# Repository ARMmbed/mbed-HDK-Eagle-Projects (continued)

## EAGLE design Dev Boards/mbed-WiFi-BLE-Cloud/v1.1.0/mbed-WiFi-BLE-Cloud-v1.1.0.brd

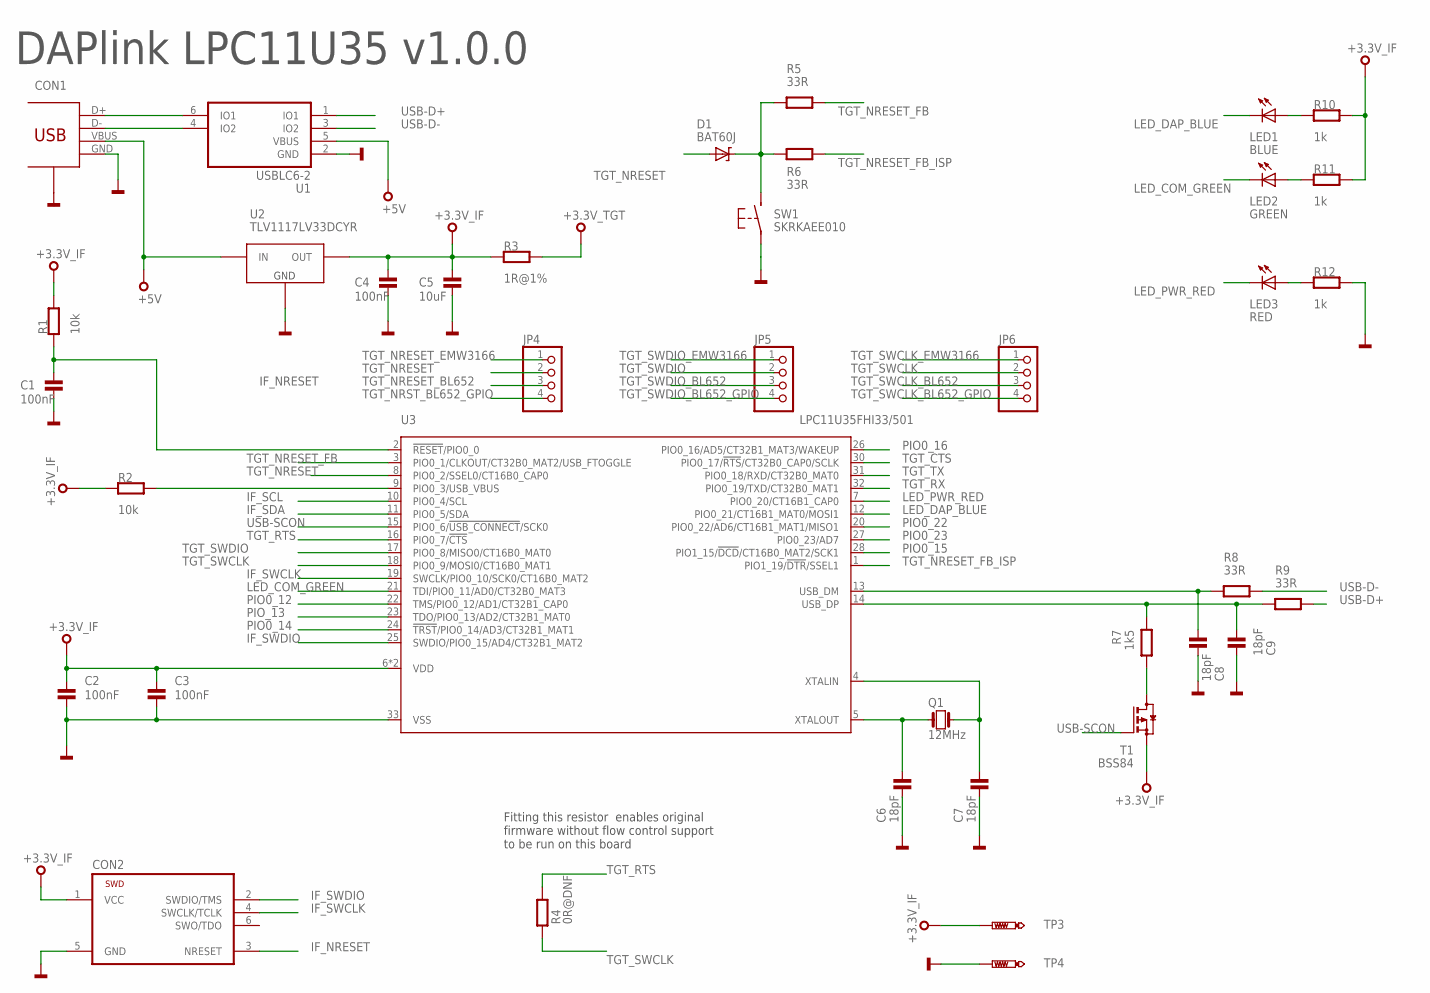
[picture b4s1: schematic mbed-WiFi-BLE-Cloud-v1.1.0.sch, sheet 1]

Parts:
C1, C2, C3, C4: 100nF; 0603
C5: 10uF; 0603
C6, C7, C8, C9: 18pF; 0603
CON1: 47346-0001; USB-MICRO-B-H
CON2: TC2030-CTX-NL
D1: BAT60J; SOD323
JP4, JP5, JP6: PINHD-1X4; 1X04
LED1: BLUE; CHIPLED_0603
LED2: GREEN; CHIPLED_0603
LED3: RED; CHIPLED_0603
Q1: 12MHz; 3.2X2.5
R1, R2: 10k; 0603
R3: 1R@1%; 0603
R4: 0R@DNF; 0603
R5, R6, R8, R9: 33R; 0603
R7: 1k5; 0603
R10, R11, R12: 1k; 0603
SW1: SKRKAEE010
T1: BSS84; SOT23-3
TP3, TP4: PTR1PAD1-13; P1-13
U1: USBLC6-2SC6; SOT23-6L
U2: TLV1117LV33DCYR; SOT223
U3: LPC11U35FHI33/501; SOT617-3

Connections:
+3.3V_IF: C2.1, C3.1, C4.1, C5.1, CON2.1 (VCC), R1.2, R2.1, R3.1, R10.2, R11.2, T1.2 (S), TP3.TP, U2.2 (OUT), U2.4 (OUT), U3.6 (VDD), U3.29 (VDD); also elsewhere on the board
+3.3V_TGT: R3.2; also elsewhere on the board
+5V: CON1.VBUS, U1.5 (VBUS), U2.3 (IN); also elsewhere on the board
GND: C1.2, C2.2, C3.2, C4.2, C5.2, C6.2, C7.2, C8.2, C9.2, CON1.GND, CON1.GND1 (SHEILD), CON1.GND2 (SHEILD), CON1.GND3 (SHEILD), CON1.GND4 (SHEILD), CON2.5 (GND), R12.2, SW1.P$1, TP4.TP, U1.2 (GND), U2.1 (GND), U3.33 (VSS); also elsewhere on the board
IF_NRESET: C1.1, CON2.3 (NRESET), R1.1, U3.2 (!RESET!/PIO0_0)
IF_SCL: U3.10 (PIO0_4/SCL); also elsewhere on the board
IF_SDA: U3.11 (PIO0_5/SDA); also elsewhere on the board
IF_SWCLK: CON2.4 (SWCLK/TCLK), U3.19 (SWCLK/PIO0_10/SCK0/CT16B0_MAT2)
IF_SWDIO: CON2.2 (SWDIO/TMS), U3.25 (SWDIO/PIO0_15/AD4/CT32B1_MAT2)
LED_COM_GREEN: LED2.C, U3.21 (TDI/PIO0_11/AD0/CT32B0_MAT3)
LED_DAP_BLUE: LED1.C, U3.12 (PIO0_21/CT16B1_MAT0/MOSI1)
LED_PWR_RED: LED3.C, U3.7 (PIO0_20/CT16B1_CAP0)
unnamed: C7.1, Q1.P$3 (2), U3.4 (XTALIN)
unnamed: R7.1, T1.3 (D)
unnamed: CON1.D+, U1.6 (IO1)
unnamed: CON1.D-, U1.4 (IO2)
unnamed: C6.1, Q1.P$1 (1), U3.5 (XTALOUT)
unnamed: R2.2, U3.9 (PIO0_3/USB_VBUS)
unnamed: LED2.A, R11.1
unnamed: LED1.A, R10.1
unnamed: LED3.A, R12.1
PIO0_12: U3.22 (TMS/PIO0_12/AD1/CT32B1_CAP0)
PIO0_14: U3.24 (!TRST!/PIO0_14/AD3/CT32B1_MAT1)
PIO0_15: U3.28 (PIO1_15/!DCD!/CT16B0_MAT2/SCK1)
PIO0_16: U3.26 (PIO0_16/AD5/CT32B1_MAT3/WAKEUP)
PIO0_22: U3.20 (PIO0_22/AD6/CT16B1_MAT1/MISO1)
PIO0_23: U3.27 (PIO0_23/AD7)
PIO_13: U3.23 (TDO/PIO0_13/AD2/CT32B1_MAT0)
TGT_CTS: U3.30 (PIO0_17/!RTS!/CT32B0_CAP0/SCLK)
TGT_NRESET: D1.A, JP4.2, U3.8 (PIO0_2/SSEL0/CT16B0_CAP0)
TGT_NRESET_BL652: JP4.3; also elsewhere on the board
TGT_NRESET_BUTTON: D1.K, R5.2, R6.2, SW1.P$2 (S)
TGT_NRESET_EMW3166: JP4.1; also elsewhere on the board
TGT_NRESET_FB: R5.1, U3.3 (PIO0_1/CLKOUT/CT32B0_MAT2/USB_FTOGGLE)
TGT_NRESET_FB_ISP: R6.1, U3.1 (PIO1_19/!DTR!/SSEL1)
TGT_NRST_BL652_GPIO: JP4.4; also elsewhere on the board
TGT_RTS: R4.2, U3.16 (PIO0_7/!CTS!)
TGT_RX: U3.32 (PIO0_19/TXD/CT32B0_MAT1); also elsewhere on the board
TGT_SWCLK: JP6.2, R4.1, U3.18 (PIO0_9/MOSI0/CT16B0_MAT1)
TGT_SWCLK_BL652: JP6.3; also elsewhere on the board
TGT_SWCLK_BL652_GPIO: JP6.4; also elsewhere on the board
TGT_SWCLK_EMW3166: JP6.1; also elsewhere on the board
TGT_SWDIO: JP5.2, U3.17 (PIO0_8/MISO0/CT16B0_MAT0)
TGT_SWDIO_BL652: JP5.3; also elsewhere on the board
TGT_SWDIO_BL652_GPIO: JP5.4; also elsewhere on the board
TGT_SWDIO_EMW3166: JP5.1; also elsewhere on the board
TGT_TX: U3.31 (PIO0_18/RXD/CT32B0_MAT0); also elsewhere on the board
USB-D+: R9.1, U1.1 (IO1)
USB-D-: R8.1, U1.3 (IO2)
USB-SCON: T1.1 (G), U3.15 (PIO0_6/!USB_CONNECT!/SCK0)
USB_DM: C8.1, R8.2, U3.13 (USB_DM)
USB_DP: C9.1, R7.2, R9.2, U3.14 (USB_DP)

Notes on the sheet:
Fitting this resistor enables original firmware without flow control support to be run on this board
DAPlink LPC11U35 v1.0.0

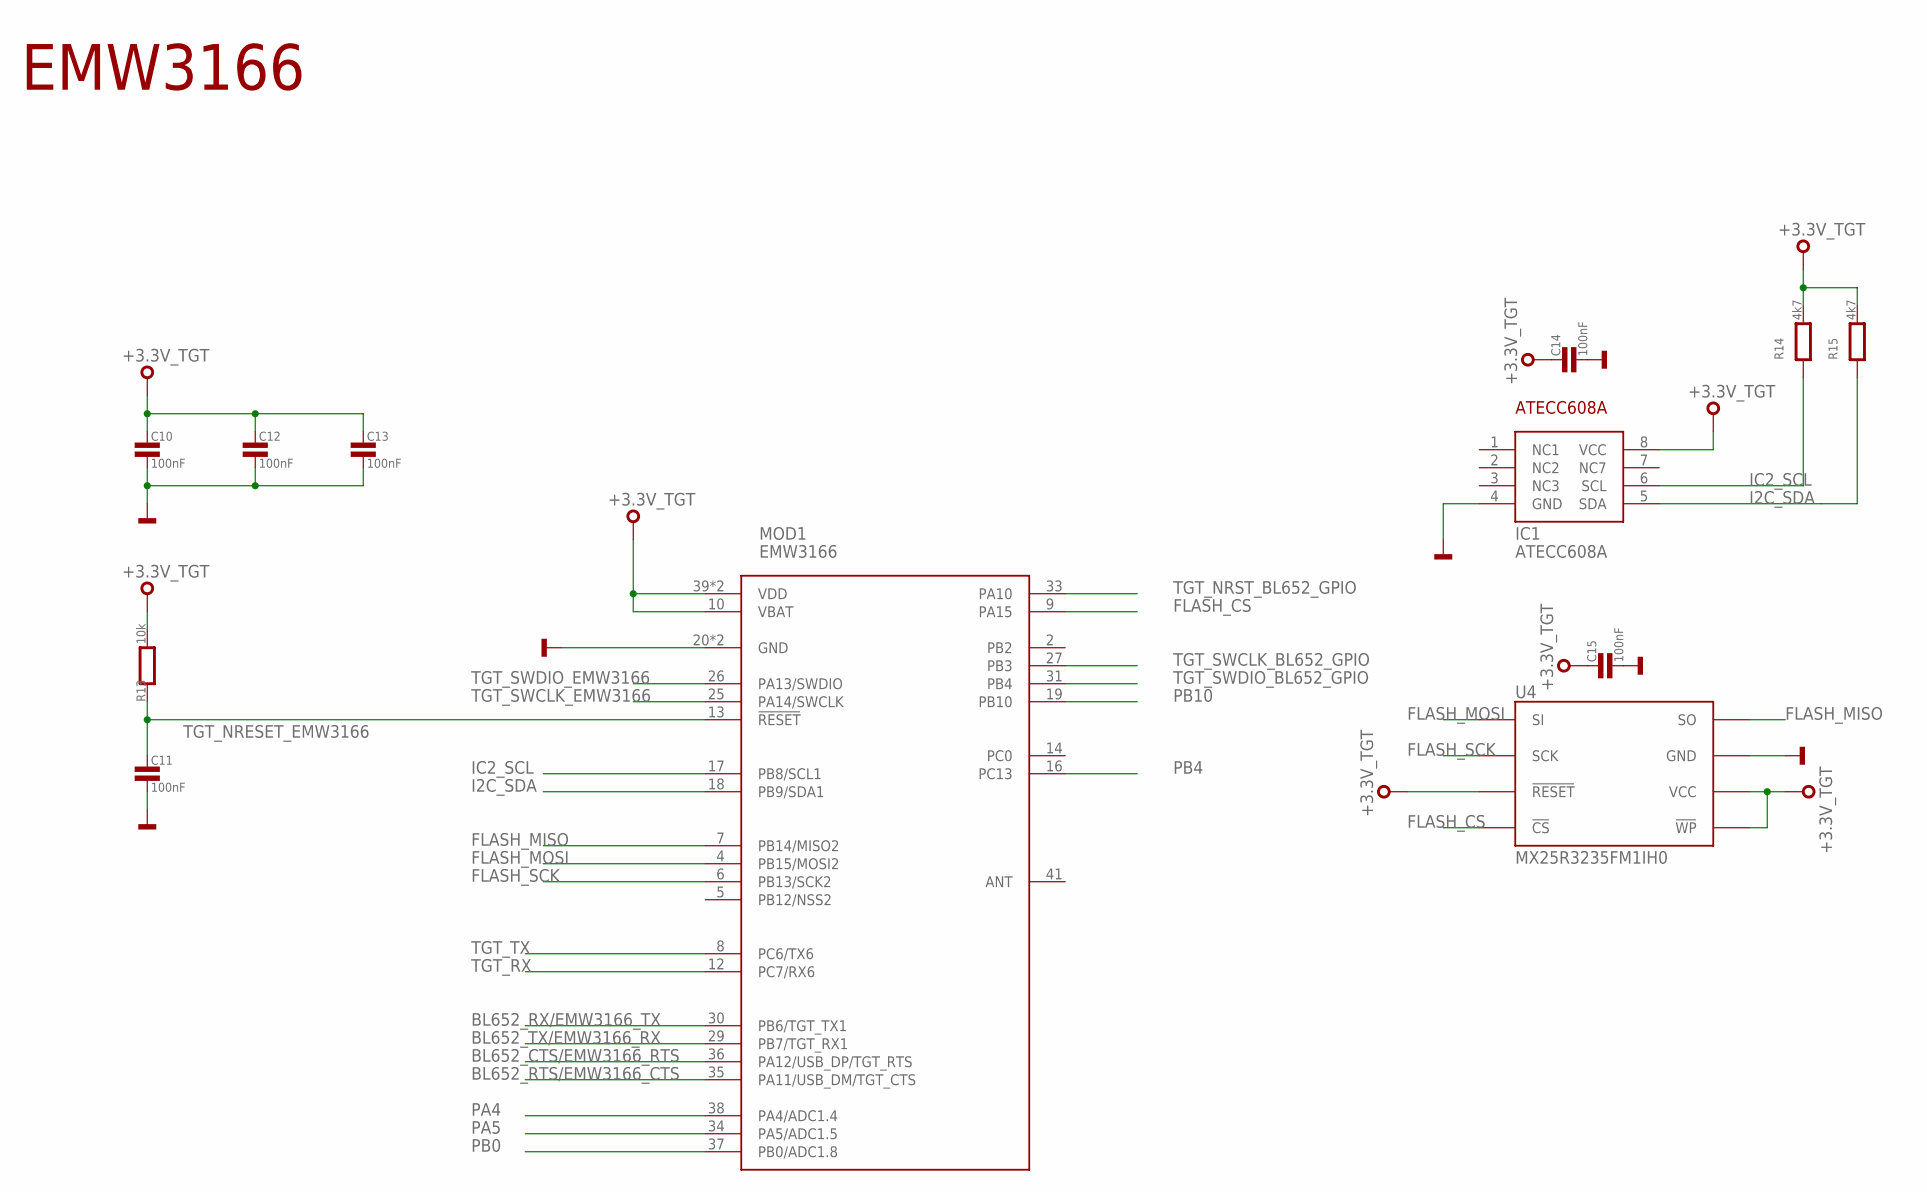
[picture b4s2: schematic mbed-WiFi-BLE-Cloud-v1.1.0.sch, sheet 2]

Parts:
C10, C11, C12, C13, C14, C15: 100nF; 0603
IC1: ATECC608A; SO8
MOD1: EMW3166
R13: 10k; 0603
R14, R15: 4k7; 0603
U4: MX25R3235FM1IH0; SO8

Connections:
+3.3V_TGT: C10.1, C12.1, C13.1, C14.1, C15.1, IC1.8 (VCC), MOD1.10 (VBAT), MOD1.39 (VDD), MOD1.40 (VDD), R13.2, R14.2, R15.2, U4.3 (!WP), U4.7 (!RESET), U4.8 (VCC); also elsewhere on the board
BL652_CTS/EMW3166_RTS: MOD1.36 (PA12/USB_DP/TGT_RTS); also elsewhere on the board
BL652_RTS/EMW3166_CTS: MOD1.35 (PA11/USB_DM/TGT_CTS); also elsewhere on the board
BL652_RX/EMW3166_TX: MOD1.30 (PB6/TGT_TX1); also elsewhere on the board
BL652_TX/EMW3166_RX: MOD1.29 (PB7/TGT_RX1); also elsewhere on the board
FLASH_CS: MOD1.9 (PA15), U4.1 (!CS)
FLASH_MISO: MOD1.7 (PB14/MISO2), U4.2 (SO)
FLASH_MOSI: MOD1.4 (PB15/MOSI2), U4.5 (SI)
FLASH_SCK: MOD1.6 (PB13/SCK2), U4.6 (SCK)
GND: C10.2, C11.2, C12.2, C13.2, C14.2, C15.2, IC1.4 (GND), MOD1.20 (GND), MOD1.21 (GND), U4.4 (GND); also elsewhere on the board
I2C_SDA: IC1.5 (SDA), MOD1.18 (PB9/SDA1), R15.1; also elsewhere on the board
IC2_SCL: IC1.6 (SCL), MOD1.17 (PB8/SCL1), R14.1; also elsewhere on the board
PA4: MOD1.38 (PA4/ADC1.4); also elsewhere on the board
PA5: MOD1.34 (PA5/ADC1.5); also elsewhere on the board
PB0: MOD1.37 (PB0/ADC1.8); also elsewhere on the board
PB4: MOD1.16 (PC13); also elsewhere on the board
PB10: MOD1.19 (PB10); also elsewhere on the board
TGT_NRESET_EMW3166: C11.1, MOD1.13 (!RESET), R13.1; also elsewhere on the board
TGT_NRST_BL652_GPIO: MOD1.33 (PA10); also elsewhere on the board
TGT_RX: MOD1.12 (PC7/RX6); also elsewhere on the board
TGT_SWCLK_BL652_GPIO: MOD1.27 (PB3); also elsewhere on the board
TGT_SWCLK_EMW3166: MOD1.25 (PA14/SWCLK); also elsewhere on the board
TGT_SWDIO_BL652_GPIO: MOD1.31 (PB4); also elsewhere on the board
TGT_SWDIO_EMW3166: MOD1.26 (PA13/SWDIO); also elsewhere on the board
TGT_TX: MOD1.8 (PC6/TX6); also elsewhere on the board

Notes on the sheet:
EMW3166

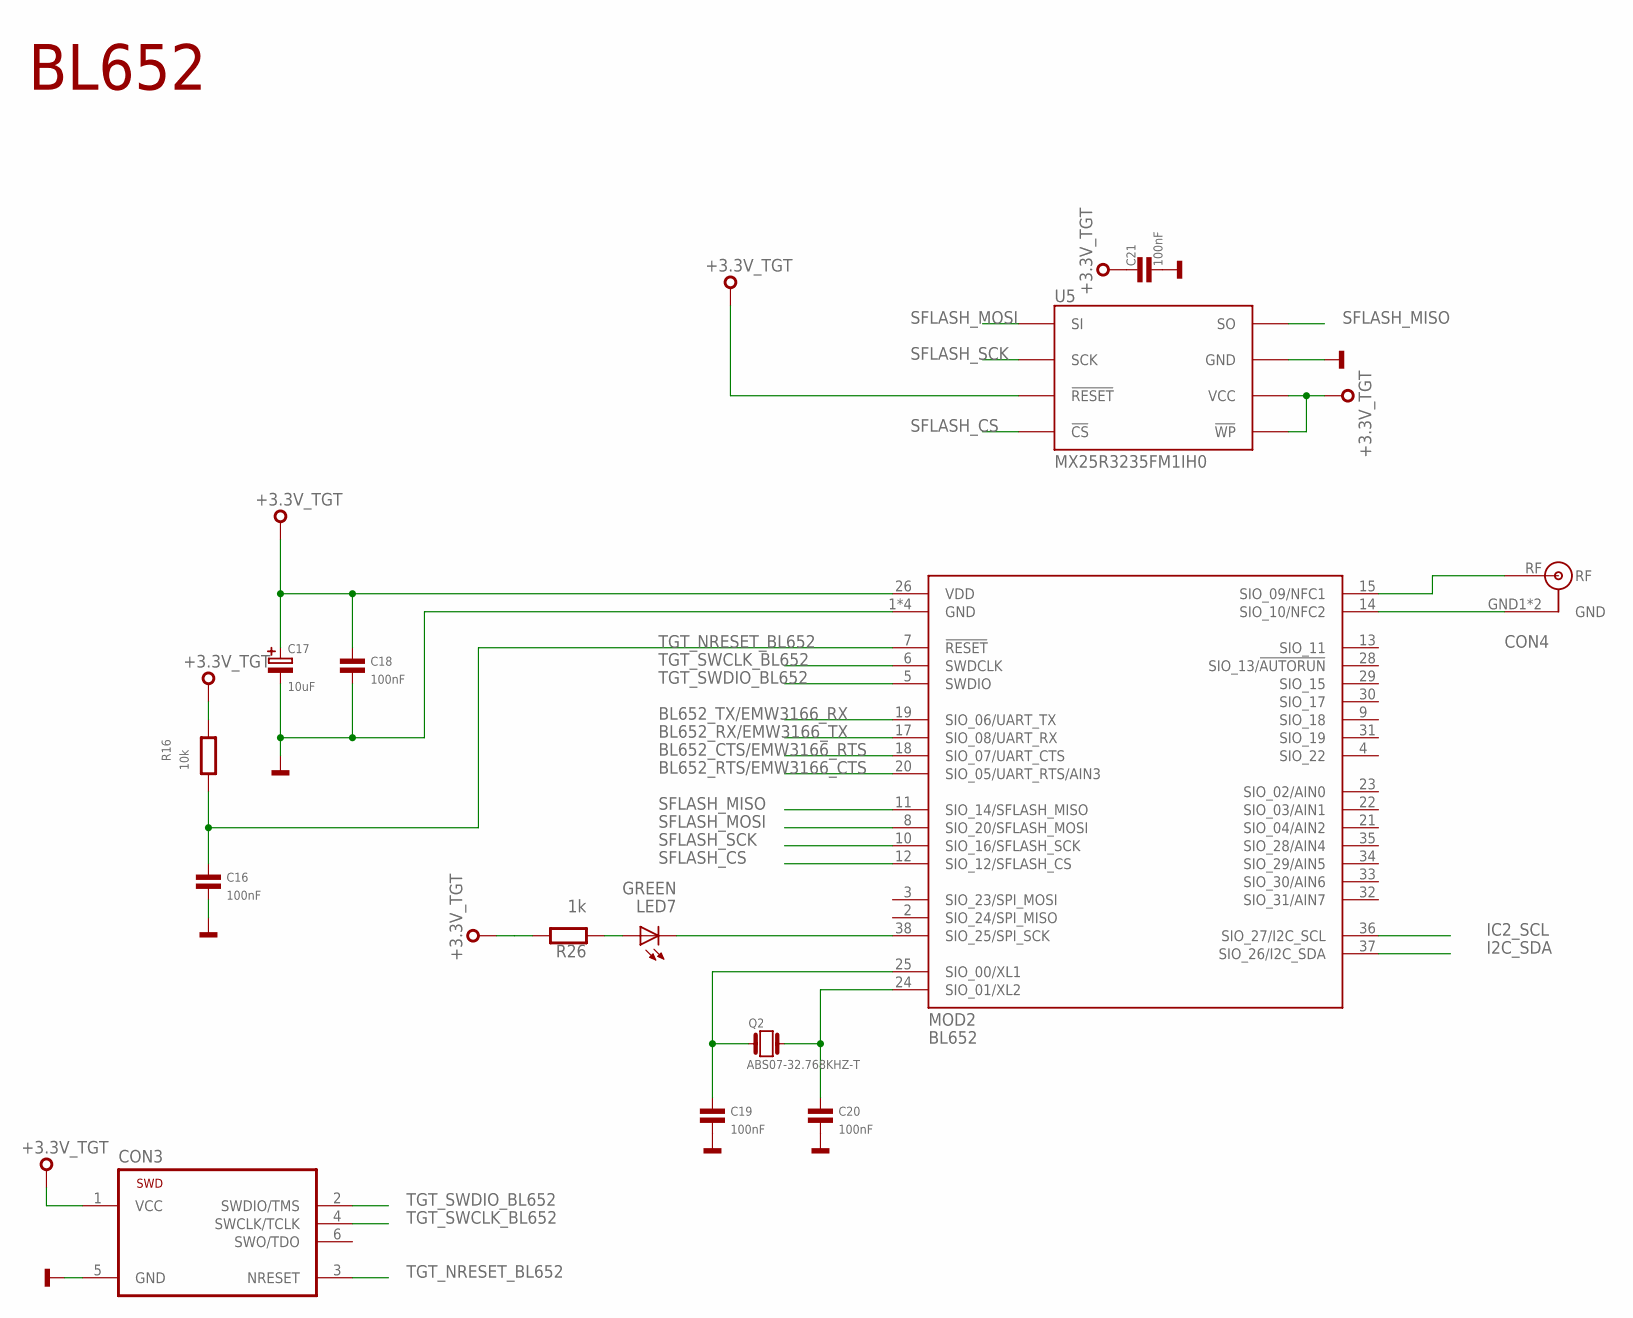
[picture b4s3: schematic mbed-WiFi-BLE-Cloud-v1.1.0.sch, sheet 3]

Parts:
C16, C18, C19, C20, C21: 100nF; 0603
C17: 10uF; SMC_B
CON3: TC2030-CTX-NL
CON4: U.FL; U.FL-R-SMT-1
LED7: GREEN; CHIPLED_0603
MOD2: BL652
Q2: ABS07-32.768KHZ-T; FC135
R16: 10k; 0603
R26: 1k; 0603
U5: MX25R3235FM1IH0; SO8

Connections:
+3.3V_TGT: C17.+, C18.1, C21.1, CON3.1 (VCC), MOD2.26 (VDD), R16.2, R26.2, U5.3 (!WP), U5.7 (!RESET), U5.8 (VCC); also elsewhere on the board
BL652_CTS/EMW3166_RTS: MOD2.18 (SIO_07/UART_CTS); also elsewhere on the board
BL652_RTS/EMW3166_CTS: MOD2.20 (SIO_05/UART_RTS/AIN3); also elsewhere on the board
BL652_RX/EMW3166_TX: MOD2.17 (SIO_08/UART_RX); also elsewhere on the board
BL652_TX/EMW3166_RX: MOD2.19 (SIO_06/UART_TX); also elsewhere on the board
GND: C16.2, C17.-, C18.2, C19.2, C20.2, C21.2, CON3.5 (GND), MOD2.1 (GND), MOD2.16 (GND), MOD2.27 (GND), MOD2.39 (GND), U5.4 (GND); also elsewhere on the board
I2C_SDA: MOD2.37 (SIO_26/I2C_SDA); also elsewhere on the board
IC2_SCL: MOD2.36 (SIO_27/I2C_SCL); also elsewhere on the board
unnamed: CON4.RF, MOD2.15 (SIO_09/NFC1)
unnamed: CON4.GND1 (GND), CON4.GND2 (GND), MOD2.14 (SIO_10/NFC2)
unnamed: LED7.A, R26.1
unnamed: LED7.C, MOD2.38 (SIO_25/SPI_SCK)
unnamed: C20.1, MOD2.24 (SIO_01/XL2), Q2.X2 (2)
unnamed: C19.1, MOD2.25 (SIO_00/XL1), Q2.X1 (1)
SFLASH_CS: MOD2.12 (SIO_12/SFLASH_CS), U5.1 (!CS)
SFLASH_MISO: MOD2.11 (SIO_14/SFLASH_MISO), U5.2 (SO)
SFLASH_MOSI: MOD2.8 (SIO_20/SFLASH_MOSI), U5.5 (SI)
SFLASH_SCK: MOD2.10 (SIO_16/SFLASH_SCK), U5.6 (SCK)
TGT_NRESET_BL652: C16.1, CON3.3 (NRESET), MOD2.7 (!RESET), R16.1; also elsewhere on the board
TGT_SWCLK_BL652: CON3.4 (SWCLK/TCLK), MOD2.6 (SWDCLK); also elsewhere on the board
TGT_SWDIO_BL652: CON3.2 (SWDIO/TMS), MOD2.5 (SWDIO); also elsewhere on the board

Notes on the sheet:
BL652

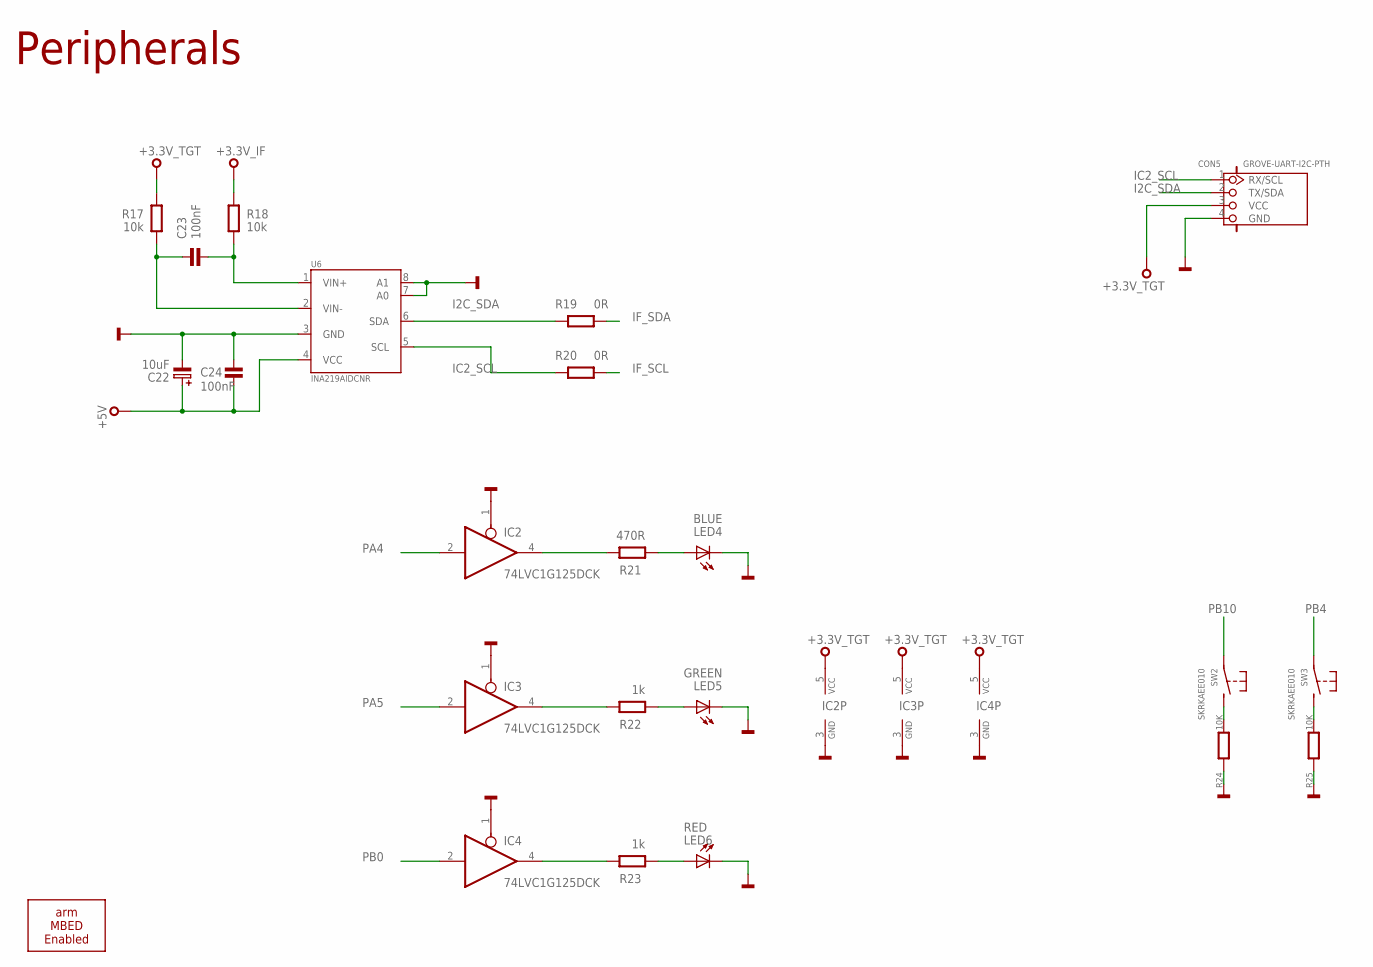
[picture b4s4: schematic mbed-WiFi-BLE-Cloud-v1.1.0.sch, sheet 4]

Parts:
C22: 10uF; SMC_B
C23, C24: 100nF; 0603
CON5: GROVE-UART-I2C-PTH; HW4-2.0
IC2, IC3, IC4: 74LVC1G125DCK; SC70-5
LED4: BLUE; CHIPLED_0603
LED5: GREEN; CHIPLED_0603
LED6: RED; CHIPLED_0603
R17, R18: 10k; 0603
R19, R20: 0R; 0603
R21: 470R; 0603
R22, R23: 1k; 0603
R24, R25: 10K; 0603
SS1: ARM-MBED-ENABLED-12MM
SW2, SW3: SKRKAEE010
U6: INA219AIDCNR; SOT23-8

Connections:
+3.3V_IF: R18.2; also elsewhere on the board
+3.3V_TGT: CON5.3 (VCC), IC2.5 (VCC), IC3.5 (VCC), IC4.5 (VCC), R17.2; also elsewhere on the board
+5V: C22.+, C24.2, U6.4 (VCC); also elsewhere on the board
GND: C22.-, C24.1, CON5.4 (GND), IC2.1 (OE), IC2.3 (GND), IC3.1 (OE), IC3.3 (GND), IC4.1 (OE), IC4.3 (GND), LED4.C, LED5.C, LED6.C, R24.1, R25.1, U6.3 (GND), U6.7 (A0), U6.8 (A1); also elsewhere on the board
I2C_SDA: CON5.2 (TX/SDA), R19.2, U6.6 (SDA); also elsewhere on the board
IC2_SCL: CON5.1 (RX/SCL), R20.2, U6.5 (SCL); also elsewhere on the board
IF_SCL: R20.1; also elsewhere on the board
IF_SDA: R19.1; also elsewhere on the board
unnamed: LED5.A, R22.2
unnamed: IC4.4 (O), R23.1
unnamed: LED6.A, R23.2
unnamed: IC3.4 (O), R22.1
unnamed: IC2.4 (O), R21.1
unnamed: LED4.A, R21.2
unnamed: C23.2, R17.1, U6.2 (VIN-)
unnamed: C23.1, R18.1, U6.1 (VIN+)
unnamed: R25.2, SW3.P$2 (S)
unnamed: R24.2, SW2.P$2 (S)
PA4: IC2.2 (I); also elsewhere on the board
PA5: IC3.2 (I); also elsewhere on the board
PB0: IC4.2 (I); also elsewhere on the board
PB4: SW3.P$1; also elsewhere on the board
PB10: SW2.P$1; also elsewhere on the board

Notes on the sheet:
Peripherals

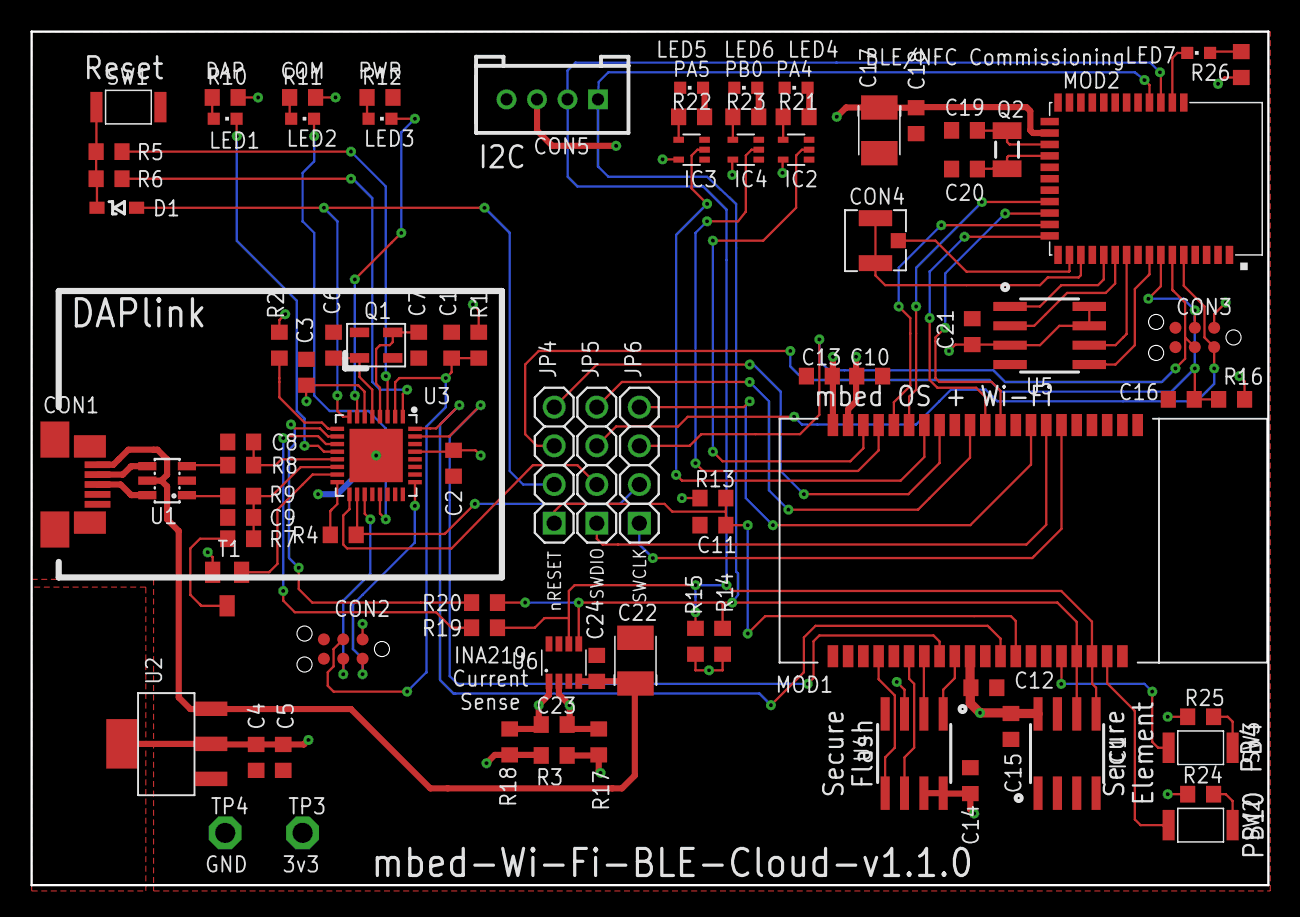
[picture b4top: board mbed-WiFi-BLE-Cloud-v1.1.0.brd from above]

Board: 2 copper layers, 81.2 x 56.0 mm, 87 parts (0 on the bottom side), 79 nets.

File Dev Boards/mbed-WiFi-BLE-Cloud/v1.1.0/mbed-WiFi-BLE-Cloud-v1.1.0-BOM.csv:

"Qty";"Value";"Device";"Package";"Parts";"Description";"MF";"MFN";"OC-DIGIKEY";"OC-MOUSER";"OC-NEWARK";"TP_SIGNAL_NAME";
"3";"";"PINHD-1X4";"1X04";"JP4, JP5, JP6";"PIN HEADER";"";"";"";"";"";"";
"2";"0R";"R0603";"0603";"R19, R20";"Resistor";"";"";"";"";"";"";
"1";"0R@DNF";"R0603";"0603";"R4";"Resistor";"";"";"";"";"";"";
"17";"100nF";"C0603";"0603";"C1, C2, C3, C4, C10, C11, C12, C13, C14, C15, C16, C18, C19, C20, C21, C23, C24";"Capacitor";"";"";"";"";"";"";
"2";"10K";"R0603";"0603";"R24, R25";"Resistor";"";"";"";"";"";"";
"6";"10k";"R0603";"0603";"R1, R2, R13, R16, R17, R18";"Resistor";"";"";"";"";"";"";
"2";"10uF";"C-POLB";"SMC_B";"C17, C22";"Polarised capacitor";"Kemet";"T491B106K020AT";"399-8298-1-ND";"80-T491B106K020";" 57K1740";"";
"1";"10uF";"C0603";"0603";"C5";"Capacitor";"";"";"";"";"";"";
"1";"12MHz";"Q_3.2X2.5";"3.2X2.5";"Q1";"Generic Crystal";"";"";"";"";"";"";
"4";"18pF";"C0603";"0603";"C6, C7, C8, C9";"Capacitor";"";"";"";"";"";"";
"1";"1R@1%";"R0603";"0603";"R3";"Resistor";"";"";"";"";"";"";
"6";"1k";"R0603";"0603";"R10, R11, R12, R22, R23, R26";"Resistor";"";"";"";"";"";"";
"1";"1k5";"R0603";"0603";"R7";"Resistor";"";"";"";"";"";"";
"4";"33R";"R0603";"0603";"R5, R6, R8, R9";"Resistor";"";"";"";"";"";"";
"1";"470R";"R0603";"0603";"R21";"Resistor";"";"";"";"";"";"";
"1";"47346-0001";"47346-0001";"USB-MICRO-B-H";"CON1";"USB Receptacle Horizontal Micro Type B";"MOLEX";"47346-0001";"WM17141CT-ND";"538-47346-0001";"1568026";"";
"2";"4k7";"R0603";"0603";"R14, R15";"Resistor";"";"";"";"";"";"";
"3";"74LVC1G125DCK";"74LVC1G125DCK";"SC70-5";"IC2, IC3, IC4";"Single Bus Buffer Gate with 3-State Output";"";"";"";"";"";"";
"1";"ABS07-32.768KHZ-T";"ABS07-32.768KHZ-T";"FC135";"Q2";"Crystal, Abracon 32.768kHz ±20ppm 12.5pF";"Abracon";"ABS07-32.768KHZ-T";"535-9542-1-ND";"535-9542-1-ND";"2101347";"";
"1";"ARM-MBED-ENABLED-12MM";"ARM-MBED-ENABLED-12MM";"ARM-MBED-ENABLED-12MM";"SS1";"";"";"";"";"";"";"";
"1";"ATECC608A";"ATECC608A";"SO8";"IC1";"";"";"";"";"";"";"";
"1";"BAT60J";"BAT60J";"SOD323";"D1";"SCHOTTKY DIODE";"STMicroelectronics";"BAT60JFILM";"497-3707-6-ND";"511-BAT60JFILM";"89K1218";"";
"1";"BL652";"BL652";"BL652";"MOD2";"";"";"";"";"";"";"";
"2";"BLUE";"LED0603";"CHIPLED_0603";"LED1, LED4";"SMD LED";"";"";"";"";"";"";
"1";"BSS84";"BSS84";"SOT23-3";"T1";"MOSFET P-CHANNEL";"Fairchild Semiconductor";"BSS84";"BSS84CT-ND";"512-BSS84";"58K8770";"";
"1";"EMW3166";"EMW3166";"EMW3166";"MOD1";"";"";"";"";"";"";"";
"3";"GREEN";"LED0603";"CHIPLED_0603";"LED2, LED5, LED7";"LED SMD";"";"";"";"";"";"";
"1";"GROVE-UART-I2C-PTH";"GROVE-UART-I2C-PTH";"HW4-2.0";"CON5";"";"";"";"";"";"";"";
"1";"INA219AIDCNR";"INA219AIDCNR";"SOT23-8";"U6";"Current Sense - I2C";"Texas Instruments";"INA219AIDCNR";"296-23770-1-ND";"595-INA219AIDCNR";"2295989";"";
"1";"LPC11U35FHI33/501";"LPC11U35FHI33/501";"SOT617-3";"U3";"32 Bit Microcontroller, ARM Cortex-M0, 50 MHz, 64 KB, 12 KB, 33 Pins, HVQFN";"NXP";"LPC11U35FHI33/501";"568-9586-ND";"771-LPC11U35FHI33501";"2115658";"";
"2";"MX25R3235FM1IH0";"MX25R3235FM1IH0";"SO8";"U4, U5";"Serial Flash 32 Mb 80 Mhz";"Macronix";"MX25R3235FM2IH0";"1092-1174-ND";"";"";"";
"2";"PTR1PAD1-13";"PTR1PAD1-13";"P1-13";"TP3, TP4";"TEST PIN";"";"";"";"";"";"";
"2";"RED";"LED0603";"CHIPLED_0603";"LED3, LED6";"SMD LED";"";"";"";"";"";"";
"3";"SKRKAEE010";"SKRKAEE010";"SKRKAEE010";"SW1, SW2, SW3";"MOMENTARY SWITCH PUSH VERTICAL (SPST)";"ALPS";"SKRKAEE010";"";"688-SKRKAE";"";"";
"2";"TC2030-CTX-NL";"TC2030-CTX-NL";"TC2030-CTX-NL";"CON2, CON3";"Tag-Connect In Circuit Programming & Debug Cable 6 Pin";"";"";"";"";"";"";
"1";"TLV1117LV33DCYR";"TLV1117LV33DCYR";"SOT223";"U2";"LDO Fixed Regulator 3.3v, 1A";"Texas Instruments";"TLV1117LV33DCYR";"296-28778-1-ND";"595-TLV1117LV33DCYR";"2323647";"";
"1";"U.FL";"U.FL";"U.FL-R-SMT-1";"CON4";"";"Hirose";"U.FL-R-SMT-1";"H9161CT-ND";"798-U.FL-R-SMT-110";"1688077";"";
"1";"USBLC6-2SC6";"USBLC6-2SC6";"SOT23-6L";"U1";"2 line Transient voltage suppressor";"STMicro";"USBLC6-2SC6Y";"497-11882-1-ND";"511-USBLC6-2SC6Y";"2629711";"";

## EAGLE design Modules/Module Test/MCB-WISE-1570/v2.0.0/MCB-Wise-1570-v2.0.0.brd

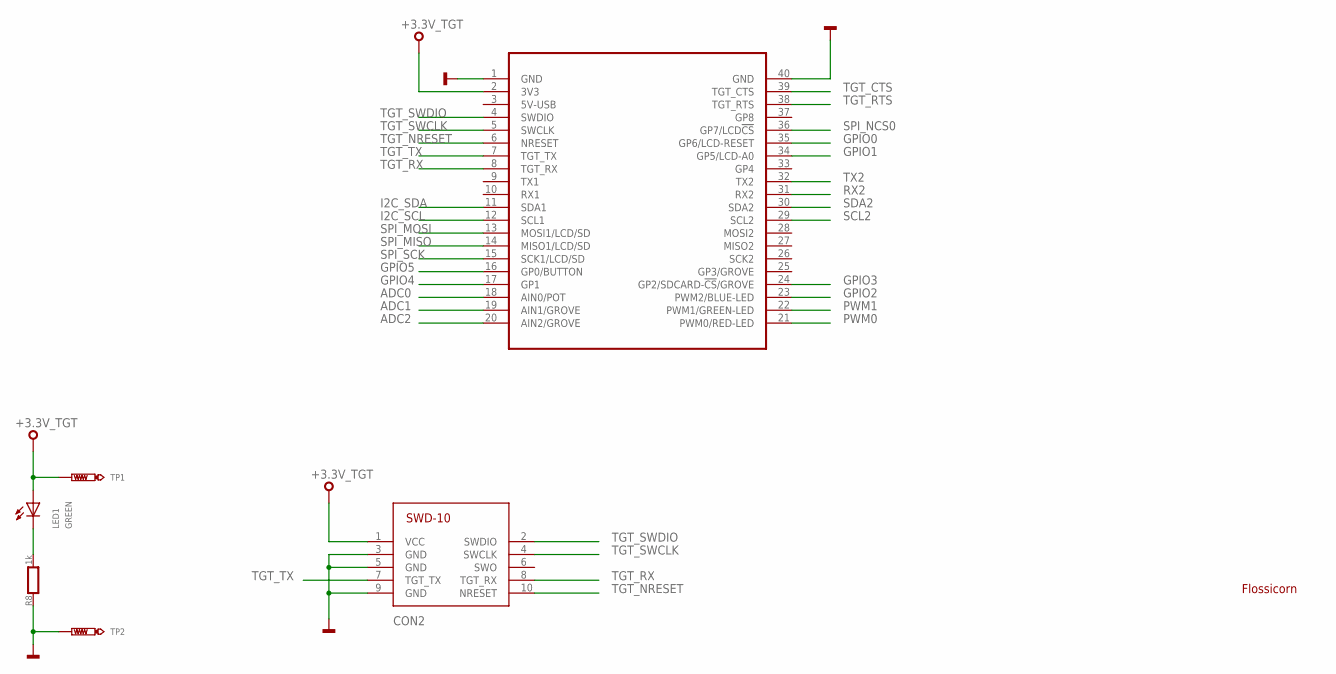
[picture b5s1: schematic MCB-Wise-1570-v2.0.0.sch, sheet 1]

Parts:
CON2: SWD-10/TC2050_SMD; FTSH-105-02
LED1: GREEN; CHIPLED_0603
MOD2: MODULE_DAUGHTER
R8: 1k; 0603
SS1: FLOSSICORN0.25; FLOSSICORN-0.25
TP1, TP2: TEST-POINT-50R-PTH; TP50-PTH

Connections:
+3.3V_TGT: CON2.1 (VCC), LED1.A, MOD2.2 (3V3), TP1.TP; also elsewhere on the board
ADC0: MOD2.18 (AIN0/POT); also elsewhere on the board
ADC1: MOD2.19 (AIN1/GROVE); also elsewhere on the board
ADC2: MOD2.20 (AIN2/GROVE); also elsewhere on the board
GND: CON2.3 (GND), CON2.5 (GND), CON2.9 (GND), MOD2.1 (GND), MOD2.40 (GND), R8.1, TP2.TP; also elsewhere on the board
GPIO0: MOD2.35 (GP6/LCD-RESET); also elsewhere on the board
GPIO1: MOD2.34 (GP5/LCD-A0); also elsewhere on the board
GPIO2: MOD2.23 (PWM2/BLUE-LED); also elsewhere on the board
GPIO3: MOD2.24 (GP2/SDCARD-!CS!/GROVE); also elsewhere on the board
GPIO4: MOD2.17 (GP1); also elsewhere on the board
GPIO5: MOD2.16 (GP0/BUTTON); also elsewhere on the board
I2C_SCL: MOD2.12 (SCL1); also elsewhere on the board
I2C_SDA: MOD2.11 (SDA1); also elsewhere on the board
PA_1: LED1.C, R8.2
PWM0: MOD2.21 (PWM0/RED-LED); also elsewhere on the board
PWM1: MOD2.22 (PWM1/GREEN-LED); also elsewhere on the board
RX2: MOD2.31 (RX2); also elsewhere on the board
SCL2: MOD2.29 (SCL2); also elsewhere on the board
SDA2: MOD2.30 (SDA2); also elsewhere on the board
SPI_MISO: MOD2.14 (MISO1/LCD/SD); also elsewhere on the board
SPI_MOSI: MOD2.13 (MOSI1/LCD/SD); also elsewhere on the board
SPI_NCS0: MOD2.36 (GP7/LCD!CS); also elsewhere on the board
SPI_SCK: MOD2.15 (SCK1/LCD/SD); also elsewhere on the board
TGT_CTS: MOD2.39 (TGT_CTS); also elsewhere on the board
TGT_NRESET: CON2.10 (NRESET), MOD2.6 (NRESET); also elsewhere on the board
TGT_RTS: MOD2.38 (TGT_RTS); also elsewhere on the board
TGT_RX: CON2.8 (TGT_RX), MOD2.8 (TGT_RX); also elsewhere on the board
TGT_SWCLK: CON2.4 (SWCLK), MOD2.5 (SWCLK); also elsewhere on the board
TGT_SWDIO: CON2.2 (SWDIO), MOD2.4 (SWDIO); also elsewhere on the board
TGT_TX: CON2.7 (TGT_TX), MOD2.7 (TGT_TX); also elsewhere on the board
TX2: MOD2.32 (TX2); also elsewhere on the board

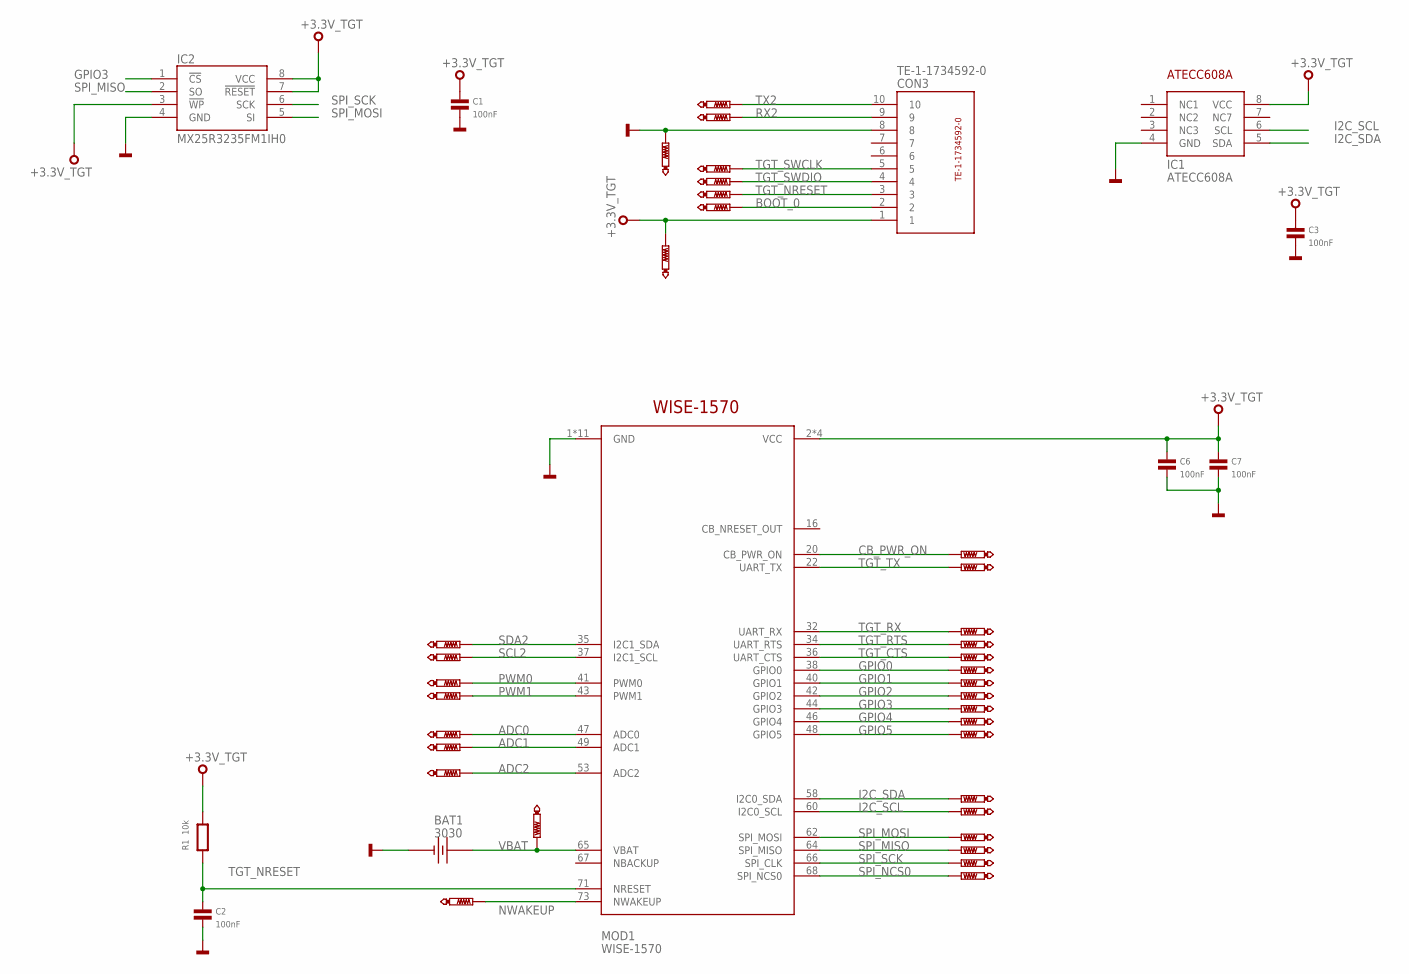
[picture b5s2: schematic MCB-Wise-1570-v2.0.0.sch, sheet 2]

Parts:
BAT1: 3030
C1, C2, C3, C6, C7: 100nF; 0603
CON3: TE-1-1734592-0
IC1: ATECC608A; SO8
IC2: MX25R3235FM1IH0; SO8
MOD1: WISE-1570; MDT420E02001
R1: 10k; 0603
TP3, TP4, TP5, TP6, TP7, TP8, TP12, TP13: PTR1TP08R; TP08R
TP9, TP10, TP11, TP14, TP15, TP16, TP17, TP18, TP19, TP20, TP21, TP22, TP23, TP24, TP25, TP26, TP27, TP28, TP29, TP30, TP31, TP32, TP33, TP34, TP35, TP36: PTR1TP07R; TP07R

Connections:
+3.3V_TGT: C1.1, C3.1, C6.1, C7.1, CON3.1, IC1.8 (VCC), IC2.3 (!WP), IC2.7 (!RESET), IC2.8 (VCC), MOD1.2 (VCC), MOD1.4 (VCC), MOD1.72 (VCC), MOD1.74 (VCC), R1.2, TP12.TP; also elsewhere on the board
ADC0: MOD1.47 (ADC0), TP29.TP; also elsewhere on the board
ADC1: MOD1.49 (ADC1), TP30.TP; also elsewhere on the board
ADC2: MOD1.53 (ADC2), TP31.TP; also elsewhere on the board
BOOT_0: CON3.2, TP8.TP
CB_PWR_ON: MOD1.20 (CB_PWR_ON), TP14.TP
GND: BAT1.-, C1.2, C2.2, C3.2, C6.2, C7.2, CON3.8, IC1.4 (GND), IC2.4 (GND), MOD1.1 (GND), MOD1.7 (GND), MOD1.18 (GND), MOD1.33 (GND), MOD1.39 (GND), MOD1.45 (GND), MOD1.51 (GND), MOD1.57 (GND), MOD1.63 (GND), MOD1.69 (GND), MOD1.75 (GND), TP13.TP; also elsewhere on the board
GPIO0: MOD1.38 (GPIO0), TP27.TP; also elsewhere on the board
GPIO1: MOD1.40 (GPIO1), TP26.TP; also elsewhere on the board
GPIO2: MOD1.42 (GPIO2), TP32.TP; also elsewhere on the board
GPIO3: IC2.1 (!CS), MOD1.44 (GPIO3), TP25.TP; also elsewhere on the board
GPIO4: MOD1.46 (GPIO4), TP24.TP; also elsewhere on the board
GPIO5: MOD1.48 (GPIO5), TP23.TP; also elsewhere on the board
I2C_SCL: IC1.6 (SCL), MOD1.60 (I2C0_SCL), TP20.TP; also elsewhere on the board
I2C_SDA: IC1.5 (SDA), MOD1.58 (I2C0_SDA), TP21.TP; also elsewhere on the board
NWAKEUP: MOD1.73 (NWAKEUP), TP34.TP
PWM0: MOD1.41 (PWM0), TP16.TP; also elsewhere on the board
PWM1: MOD1.43 (PWM1), TP17.TP; also elsewhere on the board
RX2: CON3.9, TP6.TP; also elsewhere on the board
SCL2: MOD1.37 (I2C1_SCL), TP36.TP; also elsewhere on the board
SDA2: MOD1.35 (I2C1_SDA), TP35.TP; also elsewhere on the board
SPI_MISO: IC2.2 (SO), MOD1.64 (SPI_MISO), TP11.TP; also elsewhere on the board
SPI_MOSI: IC2.5 (SI), MOD1.62 (SPI_MOSI), TP22.TP; also elsewhere on the board
SPI_NCS0: MOD1.68 (SPI_NCS0), TP9.TP; also elsewhere on the board
SPI_SCK: IC2.6 (SCK), MOD1.66 (SPI_CLK), TP10.TP; also elsewhere on the board
TGT_CTS: MOD1.36 (UART_CTS), TP19.TP; also elsewhere on the board
TGT_NRESET: C2.1, CON3.3, MOD1.71 (NRESET), R1.1, TP5.TP; also elsewhere on the board
TGT_RTS: MOD1.34 (UART_RTS), TP18.TP; also elsewhere on the board
TGT_RX: MOD1.32 (UART_RX), TP28.TP; also elsewhere on the board
TGT_SWCLK: CON3.5, TP3.TP; also elsewhere on the board
TGT_SWDIO: CON3.4, TP4.TP; also elsewhere on the board
TGT_TX: MOD1.22 (UART_TX), TP15.TP; also elsewhere on the board
TX2: CON3.10, TP7.TP; also elsewhere on the board
VBAT: BAT1.+1 (+), BAT1.+2 (+), MOD1.65 (VBAT), TP33.TP

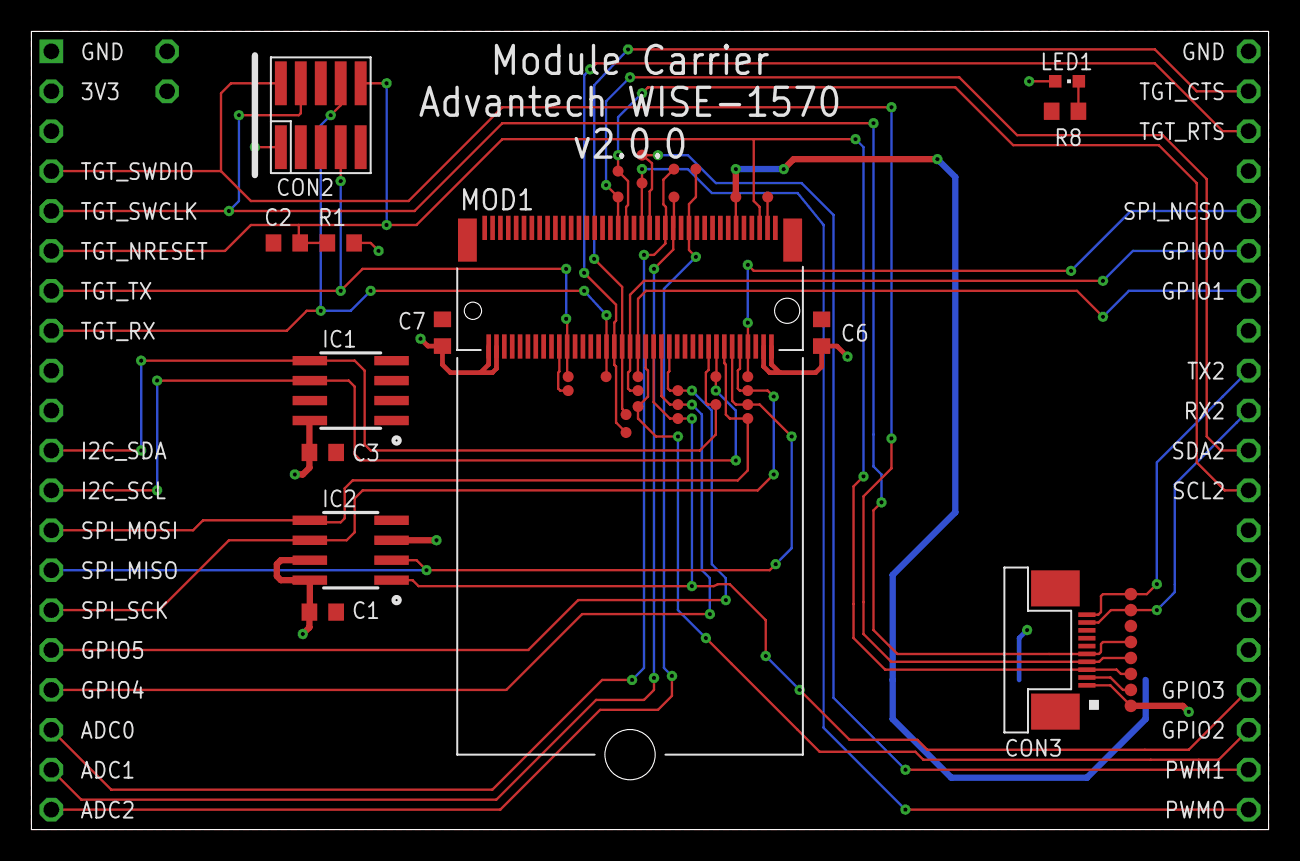
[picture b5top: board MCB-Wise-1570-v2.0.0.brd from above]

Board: 2 copper layers, 78.7 x 50.8 mm, 52 parts (1 on the bottom side), 35 nets.
